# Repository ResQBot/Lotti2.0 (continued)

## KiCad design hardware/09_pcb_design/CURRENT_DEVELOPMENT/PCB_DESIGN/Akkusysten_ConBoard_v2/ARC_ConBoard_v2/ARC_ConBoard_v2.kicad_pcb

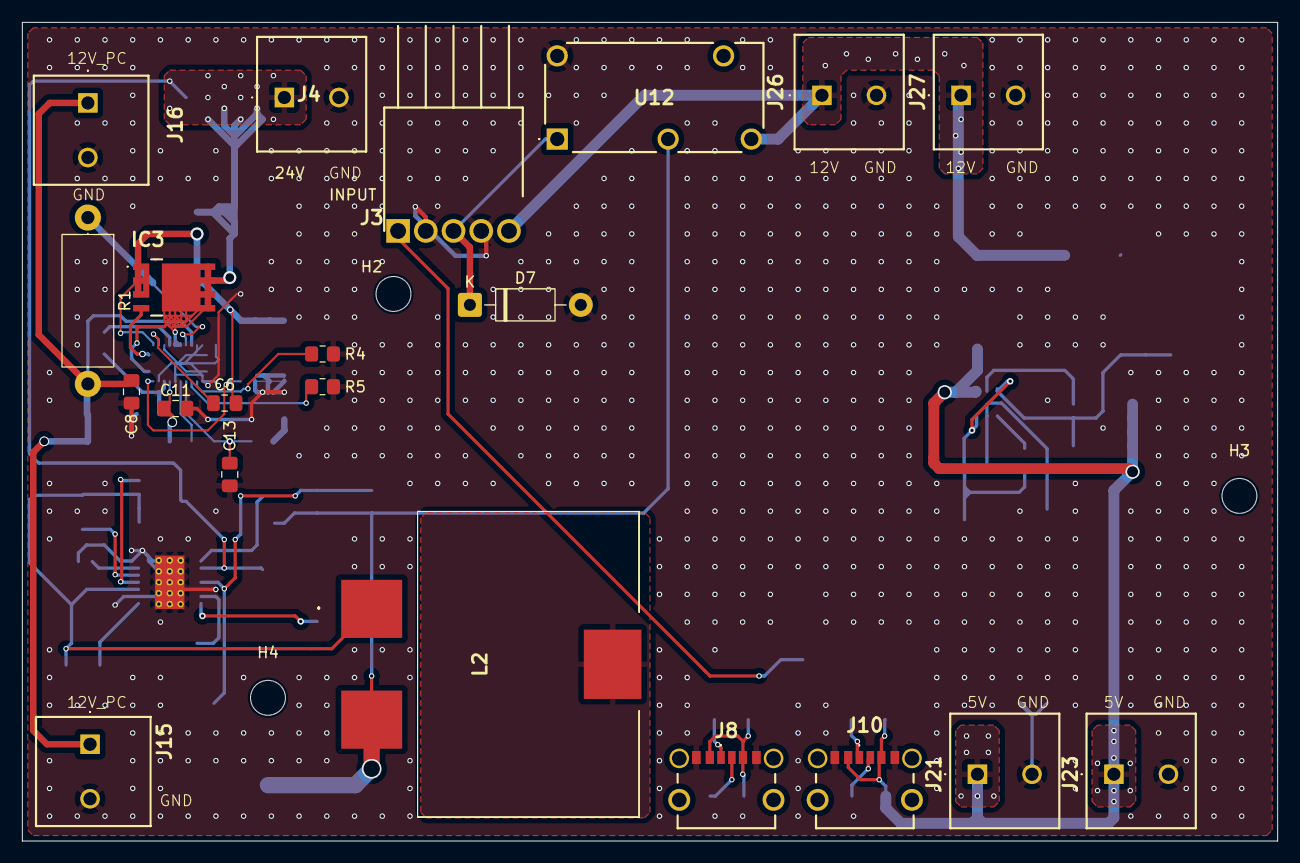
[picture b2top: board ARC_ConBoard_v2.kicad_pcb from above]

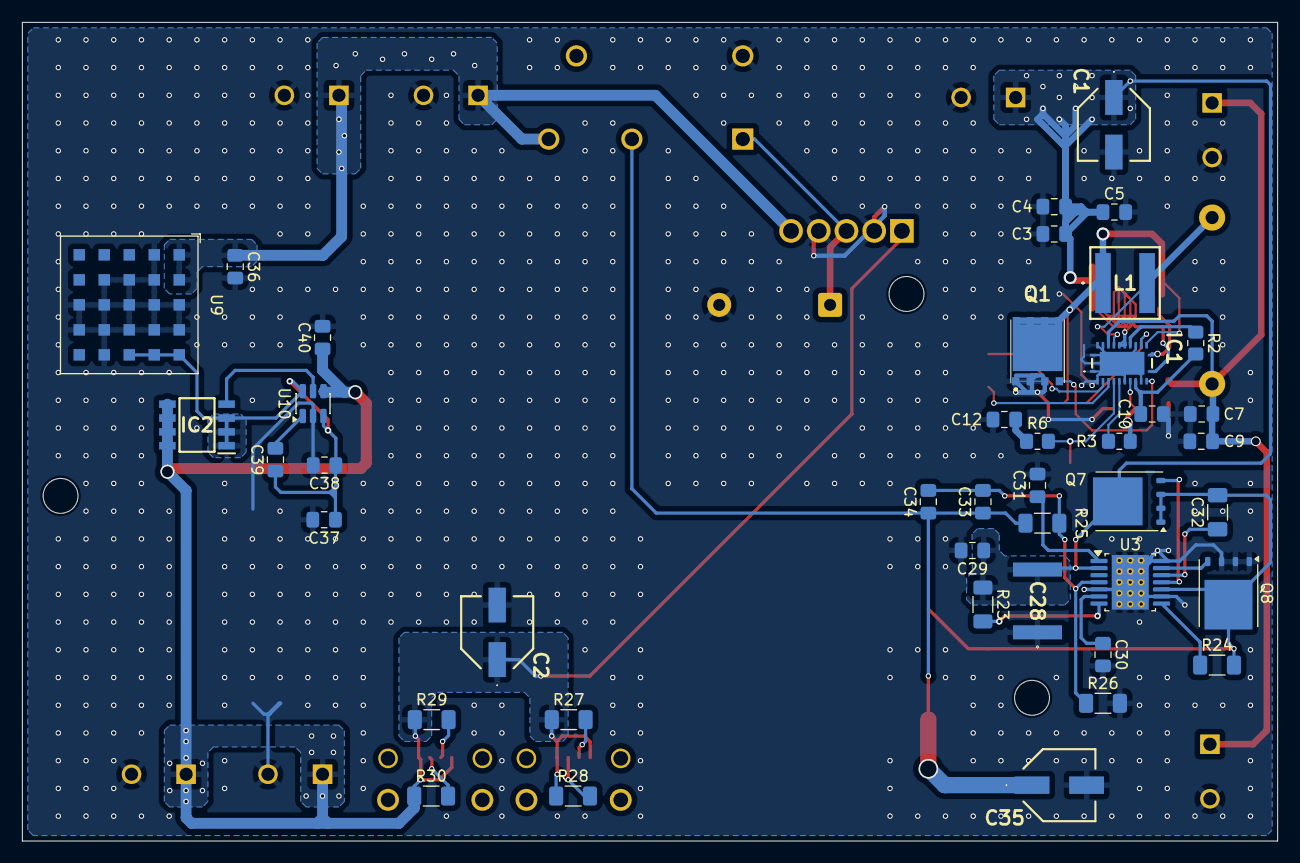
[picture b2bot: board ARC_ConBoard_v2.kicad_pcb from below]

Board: 2 copper layers, 115.0 x 75.0 mm, 66 parts (42 on the bottom side), 36 nets.

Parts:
C1, C2, C35: EEH-ZC1E560P; EEHZA1E101XP
C3, C4, C5: 4.7uF; C_0805_2012Metric_Pad1.18x1.45mm_HandSolder
C6, C11, C29, C38, C39, C40: 100nF; C_0805_2012Metric_Pad1.18x1.45mm_HandSolder
C7, C8, C9, C36: 10uF; C_0805_2012Metric_Pad1.18x1.45mm_HandSolder
C10, C31: 2.2uF; C_0805_2012Metric_Pad1.18x1.45mm_HandSolder
C12: 680pF; C_0805_2012Metric_Pad1.18x1.45mm_HandSolder
C13: 24p; C_0805_2012Metric_Pad1.18x1.45mm_HandSolder
C28: C5750X7S2A156M250KB; C5750_Commercial
C30: 15nF; C_0805_2012Metric_Pad1.18x1.45mm_HandSolder
C32: 470nF; C_1206_3216Metric_Pad1.33x1.80mm_HandSolder
C33, C34: 100pF; C_0805_2012Metric_Pad1.18x1.45mm_HandSolder
C37: 22uF; C_0805_2012Metric_Pad1.18x1.45mm_HandSolder
D7: 1N4007; D_DO-41_SOD81_P10.16mm_Horizontal
H2, H3, H4: M3_MountingHoles; MountingHole_3.2mm_M3
IC1: LM5148RGYR
IC2: FDS6690A; SOIC127P600X175-8N
IC3: IAUCN04S7L028ATMA1; IAUC120N06S5N011ATMA1
J3: 640455-5; HDRRA5W88P0X254_1X5_1270X775X610P
J4, J15, J16, J21, J23, J26, J27: 1792863
J8, J10: USB_C_Receptacle_PowerOnly_6P; UJCHGSMT2P6TR
L1: XAL6030-102MEC; XAL6030102MEC
L2: 7443641000B
Q1: CSD18514Q5A
Q7: CSD18504Q5A; TDSON-8-1
Q8: CSD18533Q5A; TDSON-8-1
R1: 5mR; R_Axial_DIN0414_L11.9mm_D4.5mm_P15.24mm_Horizontal
R2: 100k; R_0805_2012Metric_Pad1.20x1.40mm_HandSolder
R3: 47.5k; R_0805_2012Metric_Pad1.20x1.40mm_HandSolder
R4: 40.2k; R_0805_2012Metric_Pad1.20x1.40mm_HandSolder
R5: 9.53k; R_0805_2012Metric_Pad1.20x1.40mm_HandSolder
R6: 6.04k; R_0805_2012Metric_Pad1.20x1.40mm_HandSolder
R23: 348k; R_1206_3216Metric_Pad1.30x1.75mm_HandSolder
R24: 604R; R_1206_3216Metric_Pad1.30x1.75mm_HandSolder
R25: 191k; R_1206_3216Metric_Pad1.30x1.75mm_HandSolder
R26, R27, R28, R29, R30: 10k; R_1206_3216Metric_Pad1.30x1.75mm_HandSolder
U3: LM3150MH; Texas_HTSSOP-14-1EP_4.4x5mm_P0.65mm_EP3.4x5mm_Mask3.155x3.2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
U9: RPM5.0-6.0; Converter_DCDC_RECOM_RPMx.x-x.0
U10: LM74700; SOT-23-6
U12: ALQ1F24RS; ALQ112S

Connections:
/5V: C2.1 (+), C40.1, IC2.5 (D_1), IC2.6 (D_2), IC2.7 (D_3), IC2.8 (D_4), J3.1, J8.A9 (VBUS), J8.B9 (VBUS), J10.A9 (VBUS), J10.B9 (VBUS), J21.1, J23.1, R27.1, R28.1, R29.1, R30.1, U10.4 (CATHODE)
/12V: C36.1, J3.5, J26.1, J27.1, U9.A1 (+VIN), U9.A2 (+VIN), U12.3 (NO)
/12V_PC: C7.1, C8.1, C9.1, IC1.21 (VOUT), J15.1, J16.1, R1.2
/24V: C1.1 (+), C3.1, C4.1, C5.1, C28.2, C29.1, IC1.12 (VIN), IC1.18 (PFM/SYNC), IC1.19 (EN), IC3.5 (D_1), IC3.6 (D_2), IC3.7 (D_3), IC3.8 (D_4), IC3.9 (D_5), J4.1, Q7.5 (D), R23.1, U3.2 (VIN)
/EMER: D7.1 (K), J3.3, U12.1 (COIL_1)
/HiVolConversion/12V_UNSEC2: C33.1, C34.1, C35.1 (+), L2.2, R25.1, U12.2 (COM)
/HiVolConversion/2412Converter/new_12V/EXTCOMP: C13.1, IC1.5 (EXTCOMP), R6.2
/HiVolConversion/2412Converter/new_12V/MFET1_GATE: IC1.13 (HO), IC3.4 (G)
/HiVolConversion/2412Converter/new_12V/MFET1_SOURCE: C6.2, IC1.14 (SW), IC3.1 (S_1), IC3.2 (S_2), IC3.3 (S_3), IC3.10 (S_4), L1.1, Q1.5 (D_1), Q1.6 (D_2), Q1.7 (D_3), Q1.8 (D_4), Q1.9 (D_5)
/HiVolConversion/2412Converter/new_12V/MFET2_GATE: IC1.11 (LO), Q1.4 (G)
/HiVolConversion/2412Converter/new_12V/SENSE1: IC1.20 (ISNS+), L1.2, R1.1
/HiVolConversion/2412Converter/new_12V/SYNCOUT: C10.1, IC1.9 (VCC), R2.2
/LoVolConversion/5V_UNSEC: C37.1, C38.1, C39.1, IC2.1 (S_1), IC2.2 (S_2), IC2.3 (S_3), U9.A5 (+VOUT), U9.B5 (+VOUT), U9.C5 (Sense), U10.3 (EN), U10.6 (ANODE)
GND: C1.2 (-), C2.2 (-), C3.2, C4.2, C5.2, C7.2, C8.2, C9.2, C10.2, C11.2, C12.2, C13.2, C28.1, C29.2, C30.2, C31.2, C35.2 (-), C36.2, C37.2, C38.2, C40.2, D7.2 (A), IC1.1 (NC_1), IC1.2 (NC_2), IC1.7 (AGND_1), IC1.10 (PGND), IC1.16 (VCCX), IC1.22 (NC_3), IC1.23 (NC_4), IC1.24 (NC_5), IC1.25 (AGND_2), J3.2, J3.4, J4.2, J8.A12 (GND), J8.B12 (GND), J10.A12 (GND), J10.B12 (GND), J15.2, J16.2, J21.2, J23.2, J26.2, J27.2, Q1.1 (S_1), Q1.2 (S_2), Q1.3 (S_3), Q8.1 (S), Q8.2 (S), Q8.3 (S), R4.1, R5.1, R26.2, U3.5 (SGND), U3.9 (SGND), U3.14 (PGND), U3.15 (SGND), U9.A3 (GND), U9.A4 (GND), U9.B1 (GND), U9.B2 (GND), U9.B3 (GND), U9.B4 (GND), U9.C2 (GND), U9.C3 (GND), U9.C4 (GND), U9.D2 (GND), U9.D3 (GND), U9.D4 (GND), U9.D5 (GND), U9.E3 (GND), U9.E4 (GND), U10.2 (GND), U12.5 (COIL_2)
unnamed: C12.1, R6.1
unnamed: C6.1, IC1.15 (CBOOT)
unnamed: IC1.3 (CNFG), R4.2
unnamed: IC1.6 (FB), R3.1
unnamed: IC1.17 (PG/SYNCOUT), R2.1
unnamed: IC1.4 (RT), R5.2
unnamed: C11.1, IC1.8 (VDDA), R3.2
unnamed: IC2.4 (G), U10.5 (GATE)
unnamed: J8.A5 (CC1), R27.2
unnamed: J8.B5 (CC2), R28.2
unnamed: J10.A5 (CC1), R29.2
unnamed: J10.B5 (CC2), R30.2
unnamed: Q7.4 (G), U3.11 (HG)
unnamed: C32.2, L2.1, Q7.1 (S), Q7.2 (S), Q7.3 (S), Q8.5 (D), R24.2, U3.10 (SW)
unnamed: Q8.4 (G), U3.13 (LG)
unnamed: C32.1, U3.12 (BST)
unnamed: C33.2, C34.2, R25.2, R26.1, U3.4 (FB)
unnamed: R24.1, U3.8 (ILIM)
unnamed: R23.2, U3.7 (RON)
unnamed: C30.1, U3.6 (SS)
unnamed: C31.1, U3.1 (VCC)
unnamed: C39.2, U10.1 (VCAP)

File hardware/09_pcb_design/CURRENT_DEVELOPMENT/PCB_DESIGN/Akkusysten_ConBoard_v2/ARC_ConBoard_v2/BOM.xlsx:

Reference | Qty | Value | DNP | Exclude from BOM | Exclude from Board | Footprint | Datasheet | MOUSER
C1,C2,C35 | 3 | EEH-ZC1E560P |  |  |  | Bickel_STD_LIB:EEHZA1E101XP | http://industrial.panasonic.com/cdbs/www-data/pdf/RDD0000/AB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 | 667-EEH-ZC1E560P
C3,C4,C5 | 3 | 4.7uF |  |  |  | Capacitor_SMD:C_0805_2012Metric_Pad1.18x1.45mm_HandSolder | ~ | 187-CL21B475KAFNFNE
C6,C11,C29,C38,C39,C40 | 6 | 100nF |  |  |  | Capacitor_SMD:C_0805_2012Metric_Pad1.18x1.45mm_HandSolder | ~ | 187-CL21B104KCFWPJF
C7,C8,C9,C36 | 4 | 10uF |  |  |  | Capacitor_SMD:C_0805_2012Metric_Pad1.18x1.45mm_HandSolder | ~ | 187-CL21A106KAYNNNF
C10,C31 | 2 | 2.2uF |  |  |  | Capacitor_SMD:C_0805_2012Metric_Pad1.18x1.45mm_HandSolder | ~ | 187-CL21A225KAFNNNG
C12 | 1 | 680pF |  |  |  | Capacitor_SMD:C_0805_2012Metric_Pad1.18x1.45mm_HandSolder | ~ | 187-CL21B681KBANFNC
C13 | 1 | 24p |  |  |  | Capacitor_SMD:C_0805_2012Metric_Pad1.18x1.45mm_HandSolder | ~ | 187-CL21C270JB61PNC
C28 | 1 | C5750X7S2A156M250KB |  |  |  | Bickel_STD_LIB:C5750_Commercial | https://product.tdk.com/system/files/dam/doc/product/capacit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 | C5750X7S2A156M250KB
C30 | 1 | 15nF |  |  |  | Capacitor_SMD:C_0805_2012Metric_Pad1.18x1.45mm_HandSolder | ~ | 77-GA805Y153JXABC31G
C32 | 1 | 470nF |  |  |  | Capacitor_SMD:C_1206_3216Metric_Pad1.33x1.80mm_HandSolder | ~ | 581-KAF31ER71H474KU
C33,C34 | 2 | 100pF |  |  |  | Capacitor_SMD:C_0805_2012Metric_Pad1.18x1.45mm_HandSolder | ~ | 187-CL21C101JB61PNC
C37 | 1 | 22uF |  |  |  | Capacitor_SMD:C_0805_2012Metric_Pad1.18x1.45mm_HandSolder | ~ | 187-CL21A226MAYNNNE
D7 | 1 | 1N4007 |  |  |  | Diode_THT:D_DO-41_SOD81_P10.16mm_Horizontal | http://www.vishay.com/docs/88503/1n4001.pdf | 637-1N4007
H1,H2,H3,H4 | 4 | M3_MountingHoles |  | Excluded from BOM |  | MountingHole:MountingHole_3.2mm_M3 | ~ | -
IC1 | 1 | LM5148RGYR |  |  |  | Bickel_STD_LIB:LM5148RGYR | https://www.ti.com/lit/ds/symlink/lm5148.pdf?ts=168099021057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 | 595-LM5148RGYR
IC2 | 1 | FDS6690A |  |  |  | Bickel_STD_LIB:SOIC127P600X175-8N | https://www.onsemi.com/pub/Collateral/FDS6690A-D.PDF | 512-FDS6690A
IC3 | 1 | IAUCN04S7L028ATMA1 |  |  |  | Bickel_STD_LIB:IAUC120N06S5N011ATMA1 | https://www.infineon.com/dgdl/Infineon-IAUCN04S7L028-DataShe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 | 726-IAUCN04S7L028ATM
J3 | 1 | 640455-5 |  |  |  | Bickel_STD_LIB:HDRRA5W88P0X254_1X5_1270X775X610P | https://www.te.com/commerce/DocumentDelivery/DDEController?A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 | 571-6404555
J4,J15,J16,J21,J23,J26,J27 | 7 | 1792863 |  |  |  | Bickel_STD_LIB:1792863 | https://www.phoenixcontact.com/online/portal/pi/pxc/product_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 | 651-1792863
J8,J10 | 2 | USB_C_Receptacle_PowerOnly_6P |  |  |  | Bickel_STD_LIB:UJCHGSMT2P6TR | https://www.usb.org/sites/default/files/documents/usb_type-c.zip
L1 | 1 | XAL6030-102MEC |  |  |  | Bickel_STD_LIB:XAL6030102MEC | https://www.coilcraft.com/getmedia/ea51f14b-7f32-4dc6-8dfe-d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 | 994-XAL6030-102MEC
L2 | 1 | 7443641000B |  |  |  | Bickel_STD_LIB:7443641000B | https://www.we-online.com/catalog/datasheet/7443641000B.pdf
Q1 | 1 | CSD18514Q5A |  |  |  | Bickel_STD_LIB:CSD18514Q5A | http://www.ti.com/lit/gpn/csd18514q5a | 595-CSD18514Q5A
Q7 | 1 | CSD18504Q5A |  |  |  | Package_TO_SOT_SMD:TDSON-8-1 | http://www.ti.com/lit/gpn/csd18504q5a | 595-CSD18504Q5A
Q8 | 1 | CSD18533Q5A |  |  |  | Package_TO_SOT_SMD:TDSON-8-1 | http://www.ti.com/lit/gpn/csd18533q5a | 595-CSD18533Q5A
R1 | 1 | 5mR |  |  |  | Resistor_THT:R_Axial_DIN0414_L11.9mm_D4.5mm_P15.24mm_Horizontal | ~ | 588-620HR005
R2 | 1 | 100k |  |  |  | Resistor_SMD:R_0805_2012Metric_Pad1.20x1.40mm_HandSolder | ~ | 603-RE0805FRE07100KL
R3 | 1 | 47.5k |  |  |  | Resistor_SMD:R_0805_2012Metric_Pad1.20x1.40mm_HandSolder | ~ | 660-RK73H2ATTD4752F
R4 | 1 | 40.2k |  |  |  | Resistor_SMD:R_0805_2012Metric_Pad1.20x1.40mm_HandSolder | ~ | 603-RE0805FRE0740K2L
R5 | 1 | 9.53k |  |  |  | Resistor_SMD:R_0805_2012Metric_Pad1.20x1.40mm_HandSolder | ~ | 603-AC0805FR-079K53L
R6 | 1 | 6.04k |  |  |  | Resistor_SMD:R_0805_2012Metric_Pad1.20x1.40mm_HandSolder | ~ | 603-RC0805FR-076K04L
R23 | 1 | 348k |  |  |  | Resistor_SMD:R_1206_3216Metric_Pad1.30x1.75mm_HandSolder | ~ | 603-RC1206FR-07348KL
R24 | 1 | 604R |  |  |  | Resistor_SMD:R_1206_3216Metric_Pad1.30x1.75mm_HandSolder | ~ | 652-CR1206FX-6040ELF
R25 | 1 | 191k |  |  |  | Resistor_SMD:R_1206_3216Metric_Pad1.30x1.75mm_HandSolder | ~ | 603-RC1206FR-07191KL
R26,R27,R28,R29,R30 | 5 | 10k |  |  |  | Resistor_SMD:R_1206_3216Metric_Pad1.30x1.75mm_HandSolder | ~ | 603-RT1206FRE1310KL
U3 | 1 | LM3150MH |  |  |  | ARC_CONLIB_FOOTPRINT:Texas_HTSSOP-14-1EP_4.4x5mm_P0.65mm_EP3.4x5mm_Mask3.155x3.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 | http://www.ti.com/lit/ds/symlink/lm3150.pdf | 926-LM3150MH/NOPB
U9 | 1 | RPM5.0-6.0 |  |  |  | Converter_DCDC:Converter_DCDC_RECOM_RPMx.x-x.0 | https://www.recom-power.com/pdf/Innoline/RPM-6.0.pdf
U10 | 1 | LM74700 |  |  |  | Package_TO_SOT_SMD:SOT-23-6 | http://www.ti.com/lit/gpn/LM74700-Q1 | 595-LM74700QDBVRQ1
U12 | 1 | ALQ1F24RS |  |  |  | Bickel_STD_LIB:ALQ112S | https://industry.panasonic.com/ac/cdn/e/control/relay/power/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

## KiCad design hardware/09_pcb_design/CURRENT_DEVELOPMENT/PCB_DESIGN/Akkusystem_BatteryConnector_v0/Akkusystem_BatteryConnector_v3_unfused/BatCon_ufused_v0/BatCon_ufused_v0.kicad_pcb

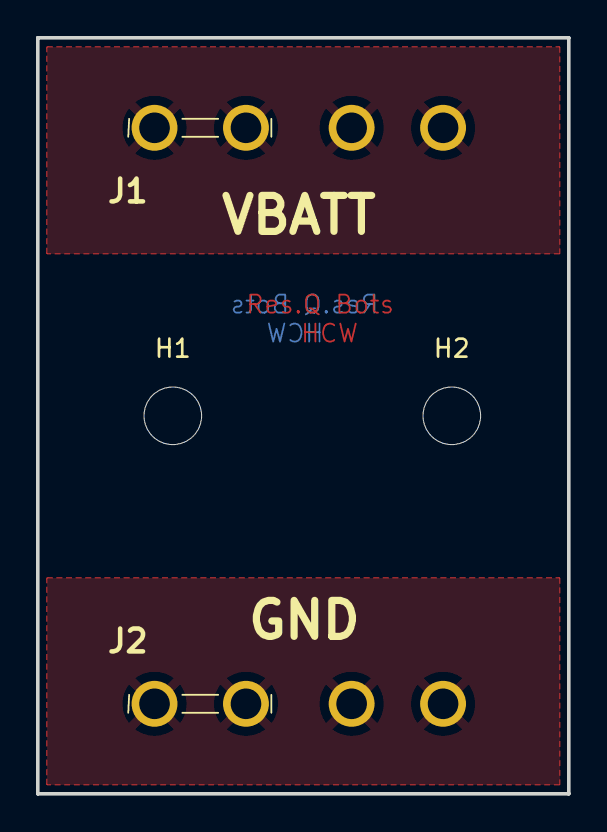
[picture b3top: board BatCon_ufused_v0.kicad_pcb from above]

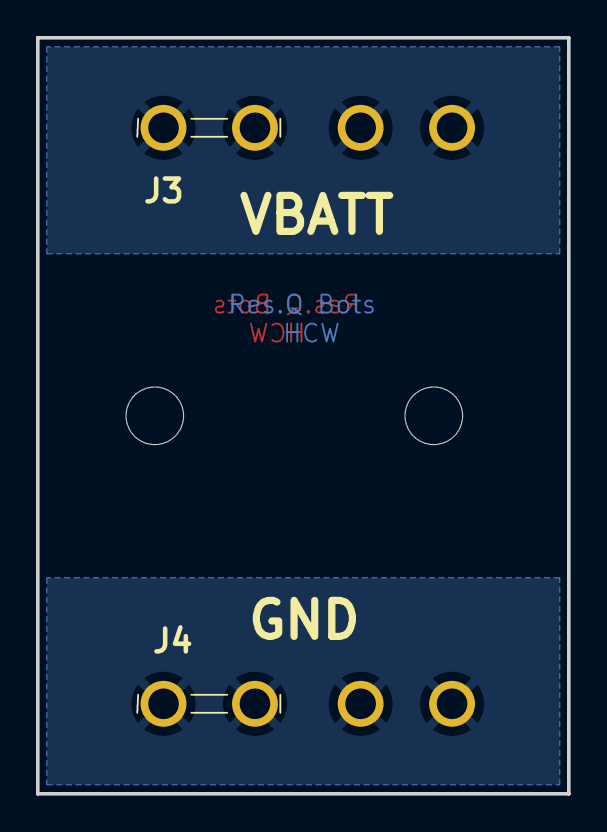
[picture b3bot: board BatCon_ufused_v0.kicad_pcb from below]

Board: 2 copper layers, 29.5 x 42.0 mm, 6 parts (2 on the bottom side), 2 nets, no tracks yet.

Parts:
H1, H2: M2; MountingHole_3.2mm_M3_DIN965
J1, J2, J3, J4: 19705-4201; 197054201

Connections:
+24V: J1.1, J1.2, J3.1, J3.2
GND: J2.1, J2.2, J4.1, J4.2

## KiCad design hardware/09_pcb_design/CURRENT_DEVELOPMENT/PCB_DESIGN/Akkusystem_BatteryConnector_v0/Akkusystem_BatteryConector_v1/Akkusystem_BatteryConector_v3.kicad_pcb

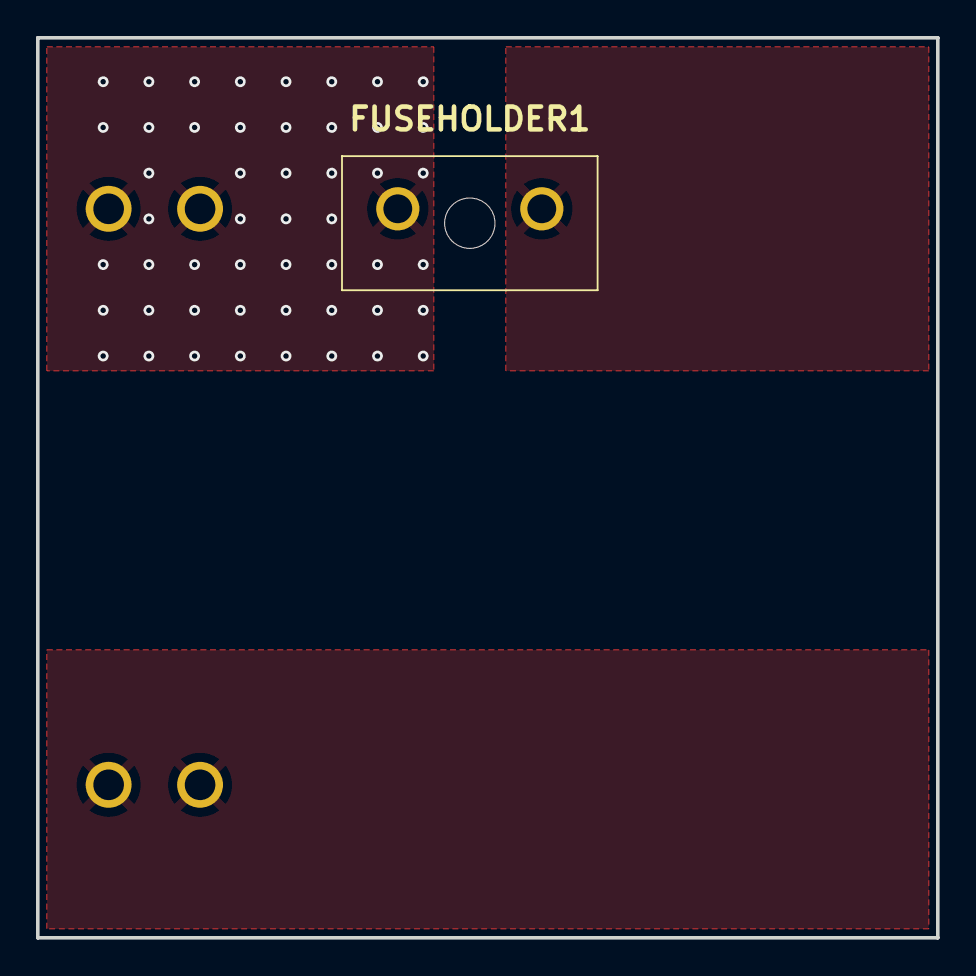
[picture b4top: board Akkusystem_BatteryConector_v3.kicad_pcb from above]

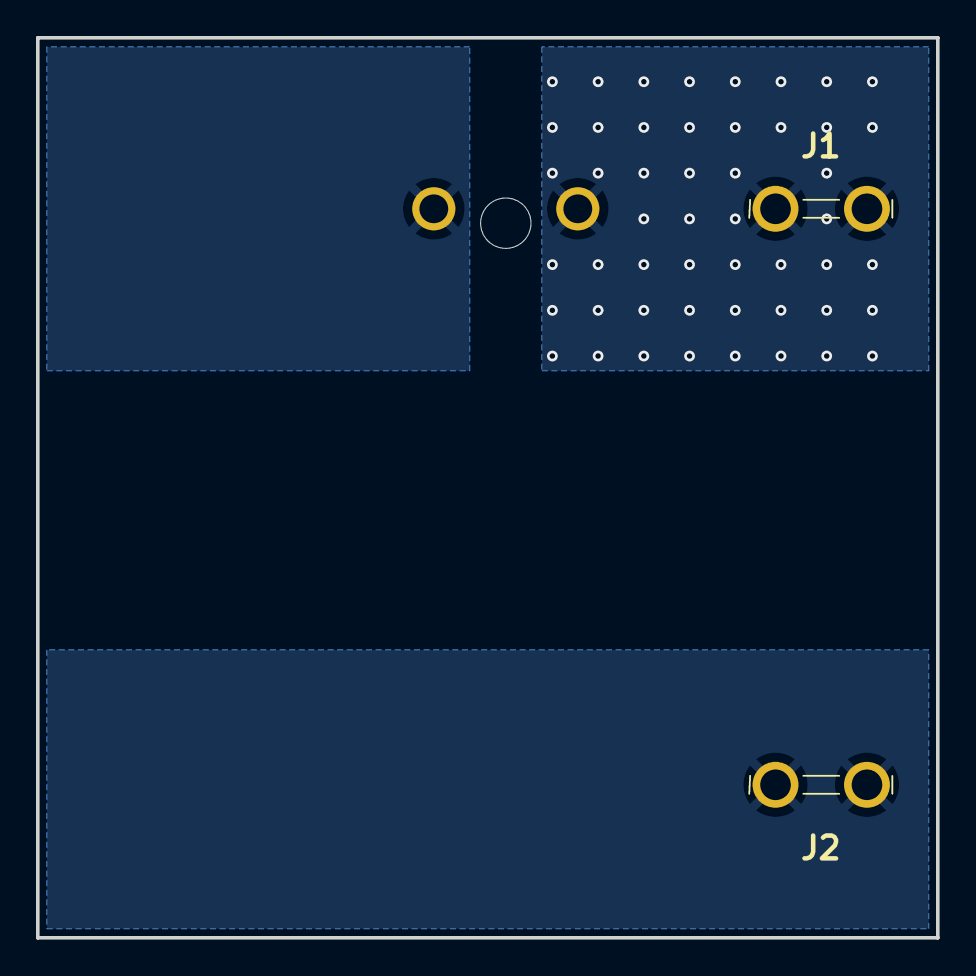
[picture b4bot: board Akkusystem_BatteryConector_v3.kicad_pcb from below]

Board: 2 copper layers, 50.0 x 50.0 mm, 3 parts (2 on the bottom side), 2 nets, no tracks yet.

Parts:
FUSEHOLDER1: 178.6764.0001; 17867640001
J1, J2: 19705-4201; 197054201

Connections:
GND: J2.1, J2.2
unnamed: FUSEHOLDER1.1, J1.1, J1.2

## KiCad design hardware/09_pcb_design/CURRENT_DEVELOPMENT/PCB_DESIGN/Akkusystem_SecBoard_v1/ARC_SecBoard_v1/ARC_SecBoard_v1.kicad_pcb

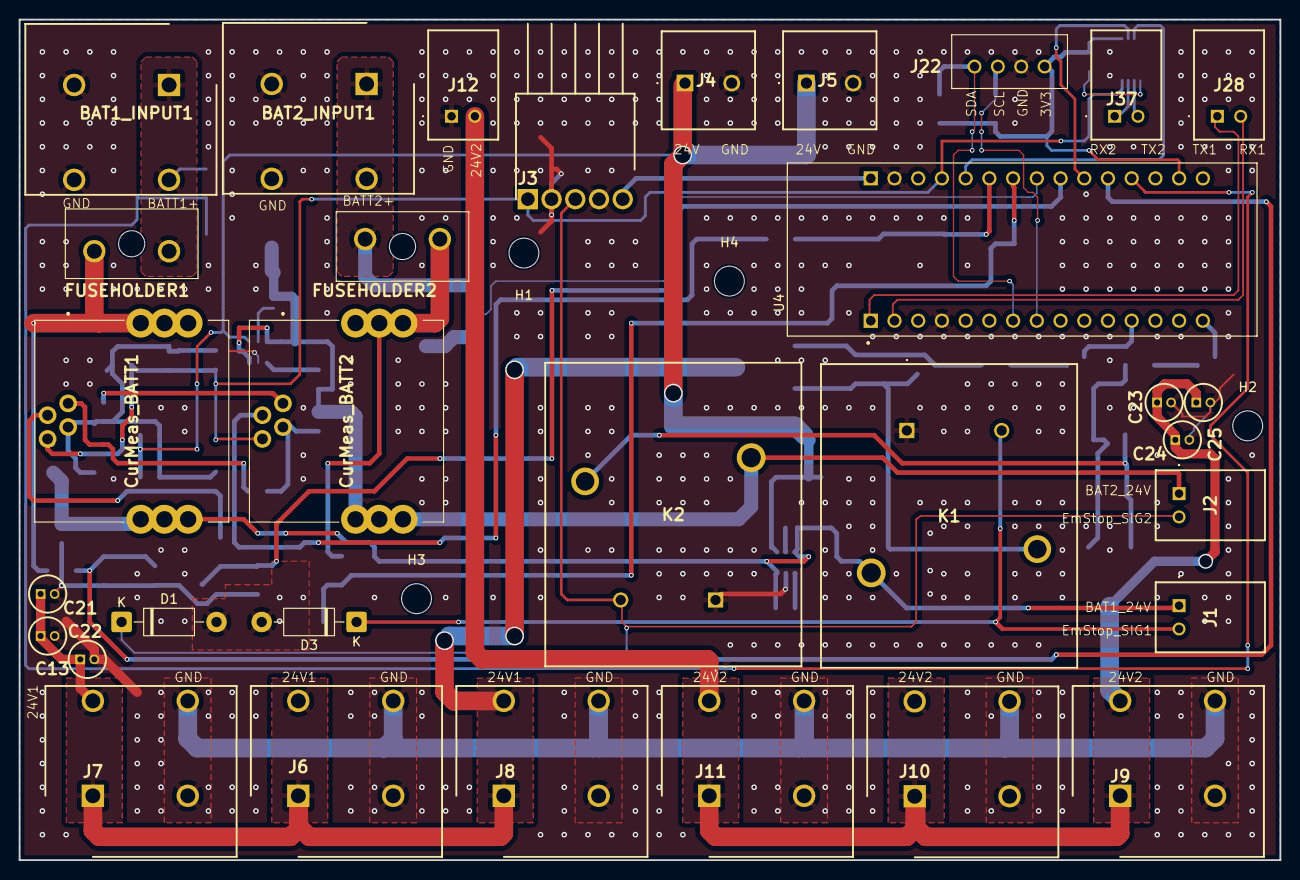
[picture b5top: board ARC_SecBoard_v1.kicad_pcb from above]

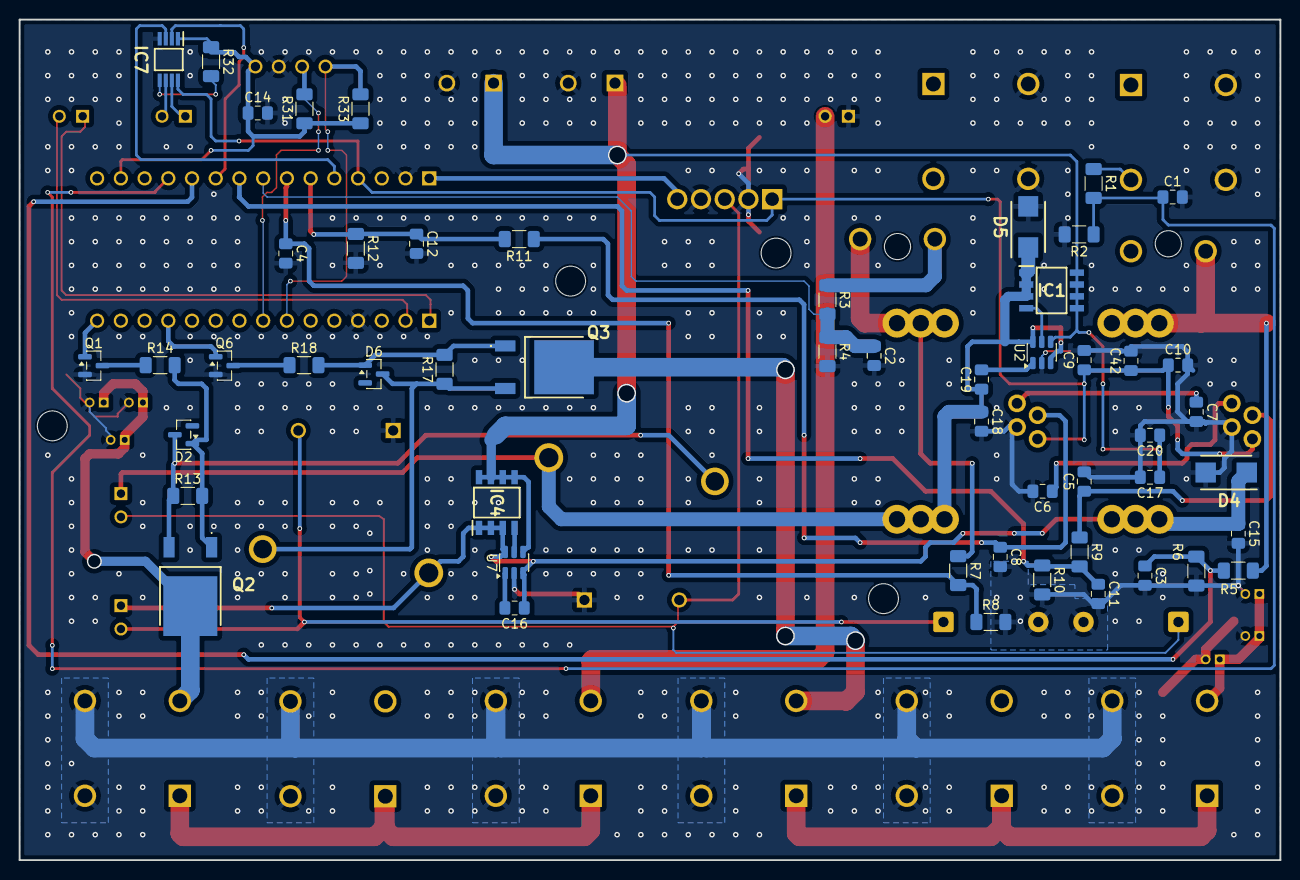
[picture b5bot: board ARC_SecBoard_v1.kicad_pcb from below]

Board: 2 copper layers, 135.0 x 90.0 mm, 88 parts (52 on the bottom side), 46 nets.

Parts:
BAT1_INPUT1, BAT2_INPUT1: VP026584000AG; SHDR4W100P1016_2X2_2032X1830X2850P
C1, C2, C3, C4, C11, C12: 1uF; C_0805_2012Metric_Pad1.18x1.45mm_HandSolder
C5, C8: 4.7nF; C_0805_2012Metric_Pad1.18x1.45mm_HandSolder
C6, C7, C9, C10, C14, C42: 47nF; C_0805_2012Metric_Pad1.18x1.45mm_HandSolder
C13, C21, C22, C23, C24, C25: ESY106M035AB2AA; CAPPRD150W45D400H850
C15, C17, C18, C20: 100nF; C_0805_2012Metric_Pad1.18x1.45mm_HandSolder
C16, C19: 0.1uF; C_0805_2012Metric_Pad1.18x1.45mm_HandSolder
CurMeas_BATT1, CurMeas_BATT2: HLSR_16-P; HLSR16P
D1, D3: 1N4007; D_DO-41_SOD81_P10.16mm_Horizontal
D2, D6: BZX84Cxx; SOT-23
D4, D5: SMBJ26A-E3_52; DIOM5436X244N
FUSEHOLDER1, FUSEHOLDER2: 30A; 17867640001
H1, H2, H3, H4: M3_MountingHoles; MountingHole_3.2mm_M3
IC1, IC4: FDS6690A; SOIC127P600X175-8N
IC7: PI4ULS5V202UEX; SOP65P490X110-8N
J1: EmerStop_Con1; 25SHB02TR
J2: EmerStop_Con2; 25SHB02TR
J3: 640455-5; HDRRA5W88P0X254_1X5_1270X775X610P
J4, J5: 1792863
J6, J7, J8, J9, J10, J11: VP026584000AG; SHDR4W100P1016_2X2_2032X1830X2850P
J12: 25SH-B-02-TR; 25SHB02TR
J22: B4B-XH-A_LF__SN_; B4BXHALFSN
J28: 25SHB02TR
J37: B2B-XH-A__LF__SN_; 25SHB02TR
K1, K2: T9AS1D12-24; T9AS1D1224
Q1, Q6: BSS138; SOT-23
Q2, Q3: IPD70P04P4L08ATMA2
R1, R3, R5, R7: 6k8; R_1206_3216Metric_Pad1.30x1.75mm_HandSolder
R2, R4, R6, R8: 1k; R_1206_3216Metric_Pad1.30x1.75mm_HandSolder
R9, R11, R14, R18: 5k1; R_1206_3216Metric_Pad1.30x1.75mm_HandSolder
R10, R12, R31, R32, R33: 10k; R_1206_3216Metric_Pad1.30x1.75mm_HandSolder
R13, R17: 100kOhm; R_1206_3216Metric_Pad1.30x1.75mm_HandSolder
U2, U7: LM74700; SOT-23-6
U4: NUCLEO-L432KC; MODULE_NUCLEO-L432KC

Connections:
+3V3: C14.1, IC7.1 (VCCA), J22.4, R31.1, R32.1, R33.1, U4.CN4_14 (+3V3)
+5V: C9.1, C10.1, C42.1, CurMeas_BATT1.4 (+UC), CurMeas_BATT2.4 (+UC), IC7.8 (VCCB), J3.1, U4.CN4_4 (+5V)
+12V: J3.5, U4.CN4_1 (VIN)
+24V: C17.1, C20.1, IC1.5 (D_1), IC1.6 (D_2), IC1.7 (D_3), IC1.8 (D_4), IC4.5 (D_1), IC4.6 (D_2), IC4.7 (D_3), IC4.8 (D_4), J4.1, J5.1, U2.4 (CATHODE), U7.4 (CATHODE)
/BattSync/MEAS_BATT1_24V: C15.1, C16.1, CurMeas_BATT1.5 (IP-_1), CurMeas_BATT1.6 (IP-_2), CurMeas_BATT1.7 (IP-_3), D4.1 (K), IC4.1 (S_1), IC4.2 (S_2), IC4.3 (S_3), J1.1, K1.4 (NO), U7.3 (EN), U7.6 (ANODE)
/BattSync/MEAS_BATT2_24V: C18.1, C19.1, CurMeas_BATT2.5 (IP-_1), CurMeas_BATT2.6 (IP-_2), CurMeas_BATT2.7 (IP-_3), D5.1 (K), IC1.1 (S_1), IC1.2 (S_2), IC1.3 (S_3), J2.1, K2.4 (NO), U2.3 (EN), U2.6 (ANODE)
/BatteryConnector/+BATT1_24V: BAT1_INPUT1.1, BAT1_INPUT1.2, FUSEHOLDER1.1, R1.1
/BatteryConnector/+BATT1_FUSED_24V: CurMeas_BATT1.8 (IP+_1), CurMeas_BATT1.9 (IP+_2), CurMeas_BATT1.10 (IP+_3), FUSEHOLDER1.2, R5.1
/BatteryConnector/+BATT2_24V: BAT2_INPUT1.1, BAT2_INPUT1.2, FUSEHOLDER2.1, R3.1
/BatteryConnector/+BATT2_FUSED_24V: CurMeas_BATT2.8 (IP+_1), CurMeas_BATT2.9 (IP+_2), CurMeas_BATT2.10 (IP+_3), FUSEHOLDER2.2, R7.1
/COMMNUNICATION/I2C1_SCL: J22.2, R31.2, U4.CN3_8 (PB6)
/COMMNUNICATION/I2C1_SDA: J22.1, R33.2, U4.CN3_7 (PB7)
/COMMNUNICATION/USART1_RX: J28.2, U4.CN3_2 (PA10)
/COMMNUNICATION/USART1_TX: J28.1, U4.CN3_1 (PA9)
/COMMNUNICATION/USART2_RX: IC7.2 (A1), U4.CN4_10 (PA3)
/COMMNUNICATION/USART2_TX: IC7.3 (A2), U4.CN4_5 (PA2)
/EmergencyStop_Connector/EmerStop_1_OUTPUT: D3.1 (K), J1.2, K1.2 (COIL_2)
/EmergencyStop_Signal: D1.1 (K), J2.2, J3.3, K2.2 (COIL_2)
/MOTOR_CONNECTOR/24V1: C13.1 (+), C21.1 (+), C22.1 (+), J6.1, J6.2, J7.1, J7.2, J8.1, J8.2, Q3.2 (D)
/MOTOR_CONNECTOR/24V2: C23.1 (+), C24.1 (+), C25.1 (+), J9.1, J9.2, J10.1, J10.2, J11.1, J11.2, J12.2, Q2.2 (D)
/SafetyControl/Current Measurement/BATT1_CurMeas_VOUT: C5.1, CurMeas_BATT1.2 (VOUT), R9.1
/SafetyControl/Current Measurement/BATT2_CurMeas_VOUT: C8.1, CurMeas_BATT2.2 (VOUT), R11.1
/SafetyControl/Current Measurement/meas_bat11: C1.1, R1.2, R2.1, U4.CN4_12 (PA0)
/SafetyControl/Current Measurement/meas_bat12: C3.1, R5.2, R6.1, U4.CN4_11 (PA1)
/SafetyControl/Current Measurement/meas_bat21: C2.1, R3.2, R4.1, U4.CN4_8 (PA5)
/SafetyControl/Current Measurement/meas_bat22: C4.1, R7.2, R8.1, U4.CN4_7 (PA6)
/SafetyControl/Current Measurement/meas_curmeas1: C11.1, R9.2, R10.1, U4.CN4_9 (PA4)
/SafetyControl/Current Measurement/meas_curmeas2: C12.1, R11.2, R12.1, U4.CN4_6 (PA7)
/SafetyControl/IO_STM_1: Q6.1 (G), U4.CN3_12 (PA8)
/SafetyControl/IO_STM_2: Q1.1 (G), U4.CN3_15 (PB4)
GND: BAT1_INPUT1.3, BAT1_INPUT1.4, BAT2_INPUT1.3, BAT2_INPUT1.4, C1.2, C2.2, C3.2, C4.2, C5.2, C6.2, C7.2, C8.2, C9.2, C10.2, C11.2, C12.2, C13.2 (-), C14.2, C15.2, C17.2, C18.2, C20.2, C21.2 (-), C22.2 (-), C23.2 (-), C24.2 (-), C25.2 (-), C42.2, CurMeas_BATT1.3 (GND-OR_0V), CurMeas_BATT2.3 (GND-OR_0V), D1.2 (A), D3.2 (A), D4.2 (A), D5.2 (A), IC7.4 (GND), J3.2, J3.4, J4.2, J5.2, J6.3, J6.4, J7.3, J7.4, J8.3, J8.4, J9.3, J9.4, J10.3, J10.4, J11.3, J11.4, J12.1, J22.3, K1.1 (COIL_1), K2.1 (COIL_1), Q1.2 (S), Q6.2 (S), R2.2, R4.2, R6.2, R8.2, R10.2, R12.2, U2.2 (GND), U4.CN3_4 (GND_CN3), U4.CN4_2 (GND_CN4), U7.2 (GND)
unnamed: C6.1, CurMeas_BATT1.1 (VREF(IN/OUT))
unnamed: C7.1, CurMeas_BATT2.1 (VREF(IN/OUT))
unnamed: D2.1 (A), Q2.1 (G), R13.2, R14.2
unnamed: D2.3 (K), K2.3 (COM), Q2.3 (S), R13.1
unnamed: D6.1 (A), Q3.1 (G), R17.2, R18.2
unnamed: D6.3 (K), K1.3 (COM), Q3.3 (S), R17.1
unnamed: IC1.4 (G), U2.5 (GATE)
unnamed: IC4.4 (G), U7.5 (GATE)
unnamed: IC7.7 (B1), J37.1
unnamed: IC7.6 (B2), J37.2
unnamed: IC7.5 (EN), R32.2
unnamed: Q1.3 (D), R14.1
unnamed: Q6.3 (D), R18.1
unnamed: C19.2, U2.1 (VCAP)
unnamed: C16.2, U7.1 (VCAP)

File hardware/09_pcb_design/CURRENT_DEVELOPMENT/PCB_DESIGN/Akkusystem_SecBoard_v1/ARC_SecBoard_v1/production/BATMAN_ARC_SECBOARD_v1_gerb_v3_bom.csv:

Designator,Footprint,Quantity,Value,LCSC Part #
"BAT1_INPUT1, BAT2_INPUT1, J10, J11, J6, J7, J8, J9",SHDR4W100P1016_2X2_2032X1830X2850P,8,VP026584000AG,
"C1, C11, C12, C2, C3, C4",0805,6,1uF,
"C10, C14, C42, C6, C7, C9",0805,6,47nF,
"C13, C21, C22, C23, C24, C25",CAPPRD150W45D400H850,6,ESY106M035AB2AA,
"C15, C17, C18, C20",0805,4,100nF,
"C16, C19",0805,2,0.1uF,
"C5, C8",0805,2,4.7nF,
"CURMEAS_BATT1, CURMEAS_BATT2",HLSR16P,2,HLSR_16-P,
"D1, D3",D_DO-41_SOD81_P10.16mm_Horizontal,2,1N4007,
"D2, D6",SOT-23,2,BZX84Cxx,
"D4, D5",DIOM5436X244N,2,SMBJ26A-E3_52,
"FUSEHOLDER1, FUSEHOLDER2",17867640001,2,30A,
"IC1, IC4",SOIC127P600X175-8N,2,FDS6690A,
IC7,SOP65P490X110-8N,1,PI4ULS5V202UEX,
J1,25SHB02TR,1,EmerStop_Con1,
J12,25SHB02TR,1,25SH-B-02-TR,
J2,25SHB02TR,1,EmerStop_Con2,
J22,B4BXHALFSN,1,B4B-XH-A_LF__SN_,
J28,25SHB02TR,1,25SHB02TR,
J3,HDRRA5W88P0X254_1X5_1270X775X610P,1,640455-5,
J37,25SHB02TR,1,B2B-XH-A__LF__SN_,
"J4, J5",1792863,2,1792863,
"K1, K2",T9AS1D1224,2,T9AS1D12-24,
"Q1, Q6",SOT-23,2,BSS138,
"Q2, Q3",IPD70P04P4L08ATMA2,2,IPD70P04P4L08ATMA2,
"R1, R3, R5, R7",1206,4,6k8,
"R10, R12, R31, R32, R33",1206,5,10k,
"R11, R14, R18, R9",1206,4,5k1,
"R13, R17",1206,2,100kOhm,
"R2, R4, R6, R8",1206,4,1k,
"U2, U7",SOT-23-6,2,LM74700,
U4,MODULE_NUCLEO-L432KC,1,NUCLEO-L432KC,

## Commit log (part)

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2026-05-27 innitial commit
2026-05-27 clean up
2026-05-28 added launch files
2026-05-28 Update .gitignore
    added Solidworks temporary files
2026-05-28 minor error correction
2026-05-29 camera implementation added
2026-05-29 name change of the package lotti vision to lotti2 vision
2026-05-29 commenting the subescrib from multi launch
2026-05-29 CAD: Added Arm
2026-05-29 folder changed
2026-06-02 servo_node working
2026-06-04 motion detection implemented in lotti vision
2026-06-05 arm working
2026-06-05 controllerbelegung angepasst
2026-06-08 fix motor updates
2026-06-09 nur noch umrechnungsfehler
2026-06-09 not sure
2026-06-09 read works now fix write
2026-06-09 motors running!!
2026-06-09 cleanup remainder of position steering
2026-06-11 chains, flippers, arm moving. need to find kp, kd, dq for flippers and arm params.
2026-06-12 drive testing
2026-06-16 arm return to zero
2026-06-16 Erster Upload CAD Body
2026-06-16 moved hardware description file
2026-06-17 'final' arm
2026-06-18 Spacer für Abdeckungen eingefügt
2026-06-18 Arm korrekt benannt und platziert
2026-06-18 Arm Getriebe und Nema hinzugefügt
2026-06-18 Main Baugruppe ergänzt
2026-06-19 Abstandshalter für seitliche Abdeckungen eingefügt
2026-06-19 fixes for murder motors and quick start scripts
2026-06-20 minor fixes
2026-06-20 cleanup and prep for tests
2026-06-20 fixed flipper controller issue and adjusted drive_interface and diff drive controller
2026-06-21 more scripts added
2026-06-21 error fix
2026-06-21 Test
2026-06-21 multi camera launch fixed
2026-06-22 stand 22 14 uhr
2026-06-22 flipper with PID controller untuned
2026-06-24 pid again
2026-06-25 pre flight check
2026-06-25 pre flight CAD
2026-06-26 added PCB Readme
2026-06-26 Added PCB Design files
2026-06-26 Renamed a file
2026-06-26 renamed some files
2026-06-26 added troubleshooting guide
2026-06-26 Dongle Halterung erstellt
2026-06-26 Abdeckung für BATMAN ergänzt
2026-06-26 Flipper neues Profil Riemenscheiben
2026-06-26 new arm camera features implementation
2026-06-28 Turm aktualisiert
2026-06-28 don't know exactly
2026-06-28 Flipper Riemenscheiben angepasst
2026-06-28 Datei durch step ersetzt (Referenzproblem)
2026-06-28 diverse Fehler beheben
2026-06-28 fehler 2
2026-06-28 Fehlerbehebungen aktives E
2026-06-28 Passives E Fehlerbehebungen
2026-06-28 Fehlerbehebung der Abdeckungen und einbau der kleinen Kettenführung unten.
2026-06-28 Spannrolle durch vorhandene ausgetauscht.
2026-06-29 start scripts and cameras
2026-06-30 flippers working (really this time)
2026-06-30 multiple minor fixes
2026-06-30 controller changes and qol
